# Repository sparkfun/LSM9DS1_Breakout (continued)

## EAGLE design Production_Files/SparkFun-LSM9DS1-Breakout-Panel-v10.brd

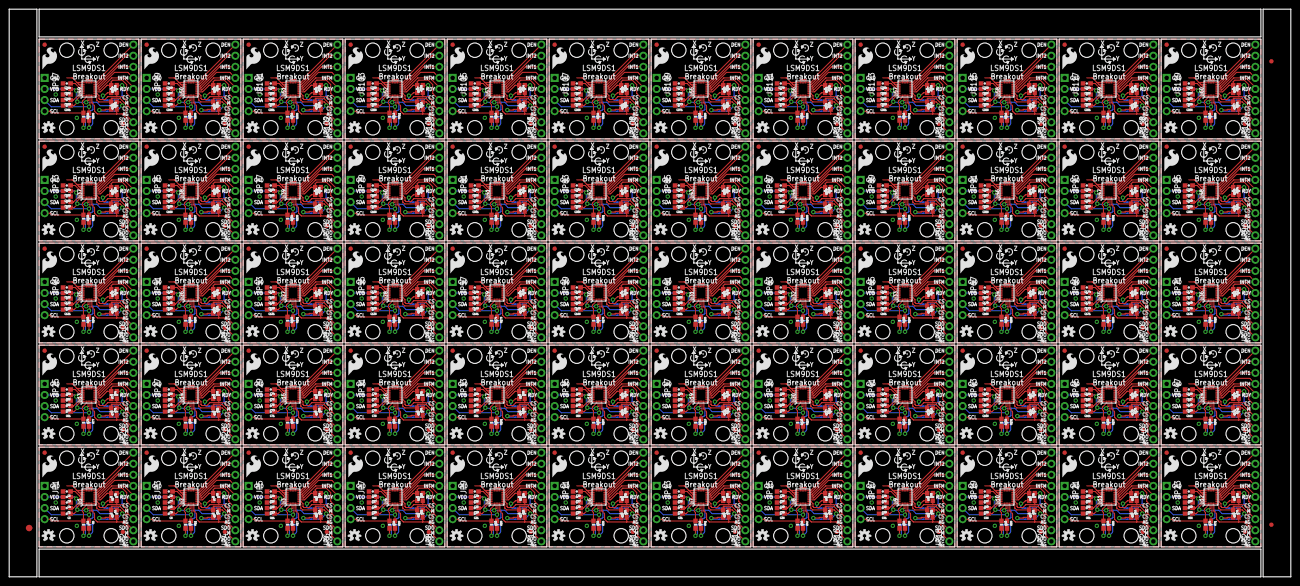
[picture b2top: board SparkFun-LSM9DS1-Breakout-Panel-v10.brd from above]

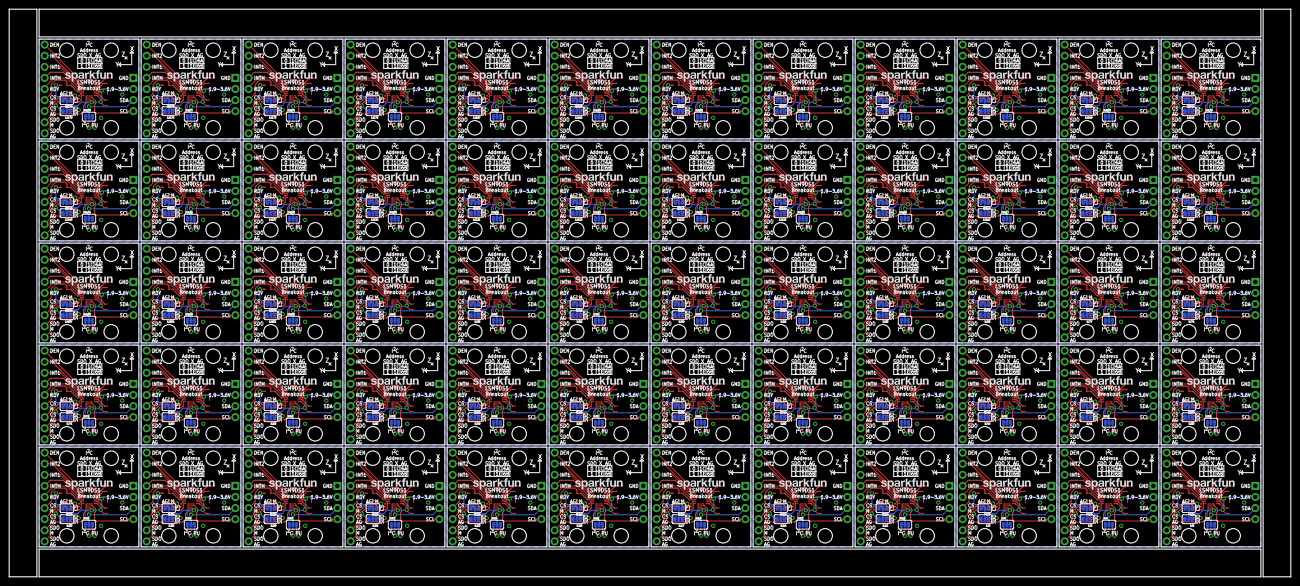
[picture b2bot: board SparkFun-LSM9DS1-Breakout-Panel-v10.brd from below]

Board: 2 copper layers, 293.6 x 130.0 mm, 1563 parts (240 on the bottom side), 1260 nets.

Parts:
C1, C2, C3, C6, C7, C8, C11, C12, C13, C16, C17, C18, C21, C22, C23, C26, C27, C28, C31, C32, C33, C36, C37, C38, C41, C42, C43, C46, C47, C48, C51, C52, C53, C56, C57, C58, C61, C62, C63, C66, C67, C68, C71, C72, C73, C76, C77, C78, C81, C82, C83, C86, C87, C88, C91, C92, C93, C96, C97, C98, C101, C102, C103, C106, C107, C108, C111, C112, C113, C116, C117, C118, C121, C122, C123, C126, C127, C128, C131, C132, C133, C136, C137, C138, C141, C142, C143, C146, C147, C148, C151, C152, C153, C156, C157, C158, C161, C162, C163, C166, C167, C168, C171, C172, C173, C176, C177, C178, C181, C182, C183, C186, C187, C188, C191, C192, C193, C196, C197, C198, C201, C202, C203, C206, C207, C208, C211, C212, C213, C216, C217, C218, C221, C222, C223, C226, C227, C228, C231, C232, C233, C236, C237, C238, C241, C242, C243, C246, C247, C248, C251, C252, C253, C256, C257, C258, C261, C262, C263, C266, C267, C268, C271, C272, C273, C276, C277, C278, C281, C282, C283, C286, C287, C288, C291, C292, C293, C296, C297, C298: 0.1uF; 0603-CAP
C4, C10, C15, C20, C25, C30, C35, C40, C45, C50, C55, C60, C65, C70, C75, C80, C85, C90, C95, C100, C105, C110, C115, C120, C125, C130, C135, C140, C145, C150, C155, C160, C165, C170, C175, C180, C185, C190, C195, C200, C205, C210, C215, C220, C225, C230, C235, C240, C245, C250, C255, C260, C265, C270, C275, C280, C285, C290, C295, C300: 10uF; 0603-CAP
C5, C9, C14, C19, C24, C29, C34, C39, C44, C49, C54, C59, C64, C69, C74, C79, C84, C89, C94, C99, C104, C109, C114, C119, C124, C129, C134, C139, C144, C149, C154, C159, C164, C169, C174, C179, C184, C189, C194, C199, C204, C209, C214, C219, C224, C229, C234, C239, C244, C249, C254, C259, C264, C269, C274, C279, C284, C289, C294, C299: 10nF; 0603-CAP
E$1: FIDUCIAL-1.5X3
E$4, E$5: FIDUCIAL-1X2
FID1, FID2, FID3, FID4, FID5, FID6, FID7, FID8, FID9, FID10, FID11, FID12, FID13, FID14, FID15, FID16, FID17, FID18, FID19, FID20, FID21, FID22, FID23, FID24, FID25, FID26, FID27, FID28, FID29, FID30, FID31, FID32, FID33, FID34, FID35, FID36, FID37, FID38, FID39, FID40, FID41, FID42, FID43, FID44, FID45, FID46, FID47, FID48, FID49, FID50, FID51, FID52, FID53, FID54, FID55, FID56, FID57, FID58, FID59, FID60, FID61, FID62, FID63, FID64, FID65, FID66, FID67, FID68, FID69, FID70, FID71, FID72, FID73, FID74, FID75, FID76, FID77, FID78, FID79, FID80, FID81, FID82, FID83, FID84, FID85, FID86, FID87, FID88, FID89, FID90, FID91, FID92, FID93, FID94, FID95, FID96, FID97, FID98, FID99, FID100, FID101, FID102, FID103, FID104, FID105, FID106, FID107, FID108, FID109, FID110, FID111, FID112, FID113, FID114, FID115, FID116, FID117, FID118, FID119, FID120: FIDUCIAL1X2; FIDUCIAL-1X2
JP1, JP3, JP5, JP7, JP9, JP11, JP13, JP15, JP17, JP19, JP21, JP23, JP25, JP27, JP29, JP31, JP33, JP35, JP37, JP39, JP41, JP43, JP45, JP47, JP49, JP51, JP53, JP55, JP57, JP59, JP61, JP63, JP65, JP67, JP69, JP71, JP73, JP75, JP77, JP79, JP81, JP83, JP85, JP87, JP89, JP91, JP93, JP95, JP97, JP99, JP101, JP103, JP105, JP107, JP109, JP111, JP113, JP115, JP117, JP119: 1X04_NO_SILK
JP2, JP4, JP6, JP8, JP10, JP12, JP14, JP16, JP18, JP20, JP22, JP24, JP26, JP28, JP30, JP32, JP34, JP36, JP38, JP40, JP42, JP44, JP46, JP48, JP50, JP52, JP54, JP56, JP58, JP60, JP62, JP64, JP66, JP68, JP70, JP72, JP74, JP76, JP78, JP80, JP82, JP84, JP86, JP88, JP90, JP92, JP94, JP96, JP98, JP100, JP102, JP104, JP106, JP108, JP110, JP112, JP114, JP116, JP118, JP120: M09NO_SILK; 1X09_NO_SILK
LOGO1, LOGO4, LOGO7, LOGO10, LOGO13, LOGO16, LOGO19, LOGO22, LOGO25, LOGO28, LOGO31, LOGO34, LOGO37, LOGO40, LOGO43, LOGO46, LOGO49, LOGO52, LOGO55, LOGO58, LOGO61, LOGO64, LOGO67, LOGO70, LOGO73, LOGO76, LOGO79, LOGO82, LOGO85, LOGO88, LOGO91, LOGO94, LOGO97, LOGO100, LOGO103, LOGO106, LOGO109, LOGO112, LOGO115, LOGO118, LOGO121, LOGO124, LOGO127, LOGO130, LOGO133, LOGO136, LOGO139, LOGO142, LOGO145, LOGO148, LOGO151, LOGO154, LOGO157, LOGO160, LOGO163, LOGO166, LOGO169, LOGO172, LOGO175, LOGO178: SFE_LOGO_NAME.1_INCH; SFE_LOGO_NAME_.1
LOGO2, LOGO5, LOGO8, LOGO11, LOGO14, LOGO17, LOGO20, LOGO23, LOGO26, LOGO29, LOGO32, LOGO35, LOGO38, LOGO41, LOGO44, LOGO47, LOGO50, LOGO53, LOGO56, LOGO59, LOGO62, LOGO65, LOGO68, LOGO71, LOGO74, LOGO77, LOGO80, LOGO83, LOGO86, LOGO89, LOGO92, LOGO95, LOGO98, LOGO101, LOGO104, LOGO107, LOGO110, LOGO113, LOGO116, LOGO119, LOGO122, LOGO125, LOGO128, LOGO131, LOGO134, LOGO137, LOGO140, LOGO143, LOGO146, LOGO149, LOGO152, LOGO155, LOGO158, LOGO161, LOGO164, LOGO167, LOGO170, LOGO173, LOGO176, LOGO179: SFE_LOGO_FLAME.2_INCH; SFE_LOGO_FLAME_.2
LOGO3, LOGO6, LOGO9, LOGO12, LOGO15, LOGO18, LOGO21, LOGO24, LOGO27, LOGO30, LOGO33, LOGO36, LOGO39, LOGO42, LOGO45, LOGO48, LOGO51, LOGO54, LOGO57, LOGO60, LOGO63, LOGO66, LOGO69, LOGO72, LOGO75, LOGO78, LOGO81, LOGO84, LOGO87, LOGO90, LOGO93, LOGO96, LOGO99, LOGO102, LOGO105, LOGO108, LOGO111, LOGO114, LOGO117, LOGO120, LOGO123, LOGO126, LOGO129, LOGO132, LOGO135, LOGO138, LOGO141, LOGO144, LOGO147, LOGO150, LOGO153, LOGO156, LOGO159, LOGO162, LOGO165, LOGO168, LOGO171, LOGO174, LOGO177, LOGO180: OSHW-LOGOS; OSHW-LOGO-S
R1, R2, R3, R4, R5, R6, R7, R8, R9, R10, R11, R12, R13, R14, R15, R16, R17, R18, R19, R20, R21, R22, R23, R24, R25, R26, R27, R28, R29, R30, R31, R32, R33, R34, R35, R36, R37, R38, R39, R40, R41, R42, R43, R44, R45, R46, R47, R48, R49, R50, R51, R52, R53, R54, R55, R56, R57, R58, R59, R60, R61, R62, R63, R64, R65, R66, R67, R68, R69, R70, R71, R72, R73, R74, R75, R76, R77, R78, R79, R80, R81, R82, R83, R84, R85, R86, R87, R88, R89, R90, R91, R92, R93, R94, R95, R96, R97, R98, R99, R100, R101, R102, R103, R104, R105, R106, R107, R108, R109, R110, R111, R112, R113, R114, R115, R116, R117, R118, R119, R120, R121, R122, R123, R124, R125, R126, R127, R128, R129, R130, R131, R132, R133, R134, R135, R136, R137, R138, R139, R140, R141, R142, R143, R144, R145, R146, R147, R148, R149, R150, R151, R152, R153, R154, R155, R156, R157, R158, R159, R160, R161, R162, R163, R164, R165, R166, R167, R168, R169, R170, R171, R172, R173, R174, R175, R176, R177, R178, R179, R180, R181, R182, R183, R184, R185, R186, R187, R188, R189, R190, R191, R192, R193, R194, R195, R196, R197, R198, R199, R200, R201, R202, R203, R204, R205, R206, R207, R208, R209, R210, R211, R212, R213, R214, R215, R216, R217, R218, R219, R220, R221, R222, R223, R224, R225, R226, R227, R228, R229, R230, R231, R232, R233, R234, R235, R236, R237, R238, R239, R240, R241, R242, R243, R244, R245, R246, R247, R248, R249, R250, R251, R252, R253, R254, R255, R256, R257, R258, R259, R260, R261, R262, R263, R264, R265, R266, R267, R268, R269, R270, R271, R272, R273, R274, R275, R276, R277, R278, R279, R280, R281, R282, R283, R284, R285, R286, R287, R288, R289, R290, R291, R292, R293, R294, R295, R296, R297, R298, R299, R300, R301, R302, R303, R304, R305, R306, R307, R308, R309, R310, R311, R312, R313, R314, R315, R316, R317, R318, R319, R320, R321, R322, R323, R324, R325, R326, R327, R328, R329, R330, R331, R332, R333, R334, R335, R336, R337, R338, R339, R340, R341, R342, R343, R344, R345, R346, R347, R348, R349, R350, R351, R352, R353, R354, R355, R356, R357, R358, R359, R360: 10K; 0603-RES
SJ1, SJ2, SJ3, SJ4, SJ5, SJ6, SJ7, SJ8, SJ9, SJ10, SJ11, SJ12, SJ13, SJ14, SJ15, SJ16, SJ17, SJ18, SJ19, SJ20, SJ21, SJ22, SJ23, SJ24, SJ25, SJ26, SJ27, SJ28, SJ29, SJ30, SJ31, SJ32, SJ33, SJ34, SJ35, SJ36, SJ37, SJ38, SJ39, SJ40, SJ41, SJ42, SJ43, SJ44, SJ45, SJ46, SJ47, SJ48, SJ49, SJ50, SJ51, SJ52, SJ53, SJ54, SJ55, SJ56, SJ57, SJ58, SJ59, SJ60, SJ61, SJ62, SJ63, SJ64, SJ65, SJ66, SJ67, SJ68, SJ69, SJ70, SJ71, SJ72, SJ73, SJ74, SJ75, SJ76, SJ77, SJ78, SJ79, SJ80, SJ81, SJ82, SJ83, SJ84, SJ85, SJ86, SJ87, SJ88, SJ89, SJ90, SJ91, SJ92, SJ93, SJ94, SJ95, SJ96, SJ97, SJ98, SJ99, SJ100, SJ101, SJ102, SJ103, SJ104, SJ105, SJ106, SJ107, SJ108, SJ109, SJ110, SJ111, SJ112, SJ113, SJ114, SJ115, SJ116, SJ117, SJ118, SJ119, SJ120, SJ121, SJ122, SJ123, SJ124, SJ125, SJ126, SJ127, SJ128, SJ129, SJ130, SJ131, SJ132, SJ133, SJ134, SJ135, SJ136, SJ137, SJ138, SJ139, SJ140, SJ141, SJ142, SJ143, SJ144, SJ145, SJ146, SJ147, SJ148, SJ149, SJ150, SJ151, SJ152, SJ153, SJ154, SJ155, SJ156, SJ157, SJ158, SJ159, SJ160, SJ161, SJ162, SJ163, SJ164, SJ165, SJ166, SJ167, SJ168, SJ169, SJ170, SJ171, SJ172, SJ173, SJ174, SJ175, SJ176, SJ177, SJ178, SJ179, SJ180: PAD-JUMPER-3-3OF3_NC_BY_TRACE_YES_SILK_FULL_BOX
STANDOFF1, STANDOFF2, STANDOFF3, STANDOFF4, STANDOFF5, STANDOFF6, STANDOFF7, STANDOFF8, STANDOFF9, STANDOFF10, STANDOFF11, STANDOFF12, STANDOFF13, STANDOFF14, STANDOFF15, STANDOFF16, STANDOFF17, STANDOFF18, STANDOFF19, STANDOFF20, STANDOFF21, STANDOFF22, STANDOFF23, STANDOFF24, STANDOFF25, STANDOFF26, STANDOFF27, STANDOFF28, STANDOFF29, STANDOFF30, STANDOFF31, STANDOFF32, STANDOFF33, STANDOFF34, STANDOFF35, STANDOFF36, STANDOFF37, STANDOFF38, STANDOFF39, STANDOFF40, STANDOFF41, STANDOFF42, STANDOFF43, STANDOFF44, STANDOFF45, STANDOFF46, STANDOFF47, STANDOFF48, STANDOFF49, STANDOFF50, STANDOFF51, STANDOFF52, STANDOFF53, STANDOFF54, STANDOFF55, STANDOFF56, STANDOFF57, STANDOFF58, STANDOFF59, STANDOFF60, STANDOFF61, STANDOFF62, STANDOFF63, STANDOFF64, STANDOFF65, STANDOFF66, STANDOFF67, STANDOFF68, STANDOFF69, STANDOFF70, STANDOFF71, STANDOFF72, STANDOFF73, STANDOFF74, STANDOFF75, STANDOFF76, STANDOFF77, STANDOFF78, STANDOFF79, STANDOFF80, STANDOFF81, STANDOFF82, STANDOFF83, STANDOFF84, STANDOFF85, STANDOFF86, STANDOFF87, STANDOFF88, STANDOFF89, STANDOFF90, STANDOFF91, STANDOFF92, STANDOFF93, STANDOFF94, STANDOFF95, STANDOFF96, STANDOFF97, STANDOFF98, STANDOFF99, STANDOFF100, STANDOFF101, STANDOFF102, STANDOFF103, STANDOFF104, STANDOFF105, STANDOFF106, STANDOFF107, STANDOFF108, STANDOFF109, STANDOFF110, STANDOFF111, STANDOFF112, STANDOFF113, STANDOFF114, STANDOFF115, STANDOFF116, STANDOFF117, STANDOFF118, STANDOFF119, STANDOFF120, STANDOFF121, STANDOFF122, STANDOFF123, STANDOFF124, STANDOFF125, STANDOFF126, STANDOFF127, STANDOFF128, STANDOFF129, STANDOFF130, STANDOFF131, STANDOFF132, STANDOFF133, STANDOFF134, STANDOFF135, STANDOFF136, STANDOFF137, STANDOFF138, STANDOFF139, STANDOFF140, STANDOFF141, STANDOFF142, STANDOFF143, STANDOFF144, STANDOFF145, STANDOFF146, STANDOFF147, STANDOFF148, STANDOFF149, STANDOFF150, STANDOFF151, STANDOFF152, STANDOFF153, STANDOFF154, STANDOFF155, STANDOFF156, STANDOFF157, STANDOFF158, STANDOFF159, STANDOFF160, STANDOFF161, STANDOFF162, STANDOFF163, STANDOFF164, STANDOFF165, STANDOFF166, STANDOFF167, STANDOFF168, STANDOFF169, STANDOFF170, STANDOFF171, STANDOFF172, STANDOFF173, STANDOFF174, STANDOFF175, STANDOFF176, STANDOFF177, STANDOFF178, STANDOFF179, STANDOFF180, STANDOFF181, STANDOFF182, STANDOFF183, STANDOFF184, STANDOFF185, STANDOFF186, STANDOFF187, STANDOFF188, STANDOFF189, STANDOFF190, STANDOFF191, STANDOFF192, STANDOFF193, STANDOFF194, STANDOFF195, STANDOFF196, STANDOFF197, STANDOFF198, STANDOFF199, STANDOFF200, STANDOFF201, STANDOFF202, STANDOFF203, STANDOFF204, STANDOFF205, STANDOFF206, STANDOFF207, STANDOFF208, STANDOFF209, STANDOFF210, STANDOFF211, STANDOFF212, STANDOFF213, STANDOFF214, STANDOFF215, STANDOFF216, STANDOFF217, STANDOFF218, STANDOFF219, STANDOFF220, STANDOFF221, STANDOFF222, STANDOFF223, STANDOFF224, STANDOFF225, STANDOFF226, STANDOFF227, STANDOFF228, STANDOFF229, STANDOFF230, STANDOFF231, STANDOFF232, STANDOFF233, STANDOFF234, STANDOFF235, STANDOFF236, STANDOFF237, STANDOFF238, STANDOFF239, STANDOFF240: STAND-OFF
U1, U2, U3, U4, U5, U6, U7, U8, U9, U10, U11, U12, U13, U14, U15, U16, U17, U18, U19, U20, U21, U22, U23, U24, U25, U26, U27, U28, U29, U30, U31, U32, U33, U34, U35, U36, U37, U38, U39, U40, U41, U42, U43, U44, U45, U46, U47, U48, U49, U50, U51, U52, U53, U54, U55, U56, U57, U58, U59, U60: LSM9DS1; LGA24-8X4

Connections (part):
C1: C1.1, U1.24
C2: C8.1, U2.24
C3: C13.1, U3.24
C4: C18.1, U4.24
C5: C23.1, U5.24
C6: C28.1, U6.24
C7: C33.1, U7.24
C8: C38.1, U8.24
C9: C43.1, U9.24
C10: C48.1, U10.24
C11: C53.1, U11.24
C12: C58.1, U12.24
C13: C63.1, U13.24
C14: C68.1, U14.24
C15: C73.1, U15.24
C16: C78.1, U16.24
C17: C83.1, U17.24
C18: C88.1, U18.24
C19: C93.1, U19.24
C20: C98.1, U20.24
C21: C103.1, U21.24
C22: C108.1, U22.24
C23: C113.1, U23.24
C24: C118.1, U24.24
C25: C123.1, U25.24
C26: C128.1, U26.24
C27: C133.1, U27.24
C28: C138.1, U28.24
C29: C143.1, U29.24
C30: C148.1, U30.24
C31: C153.1, U31.24
C32: C158.1, U32.24
C33: C163.1, U33.24
C34: C168.1, U34.24
C35: C173.1, U35.24
C36: C178.1, U36.24
C37: C183.1, U37.24
C38: C188.1, U38.24
C39: C193.1, U39.24
C40: C198.1, U40.24
C41: C203.1, U41.24
C42: C208.1, U42.24
C43: C213.1, U43.24
C44: C218.1, U44.24
C45: C223.1, U45.24
C46: C228.1, U46.24
C47: C233.1, U47.24
C48: C238.1, U48.24
C49: C243.1, U49.24
C50: C248.1, U50.24
C51: C253.1, U51.24
C52: C258.1, U52.24
C53: C263.1, U53.24
C54: C268.1, U54.24
C55: C273.1, U55.24
C56: C278.1, U56.24
C57: C283.1, U57.24
C58: C288.1, U58.24
C59: C293.1, U59.24
C60: C298.1, U60.24
CAP: C5.1, U1.21
CAP1: C9.1, U2.21
CAP2: C14.1, U3.21
CAP3: C19.1, U4.21
CAP4: C24.1, U5.21
CAP5: C29.1, U6.21
CAP6: C34.1, U7.21
CAP7: C39.1, U8.21
CAP8: C44.1, U9.21
CAP9: C49.1, U10.21
CAP10: C54.1, U11.21
CAP11: C59.1, U12.21
CAP12: C64.1, U13.21
CAP13: C69.1, U14.21
CAP14: C74.1, U15.21
CAP15: C79.1, U16.21
CAP16: C84.1, U17.21
CAP17: C89.1, U18.21
CAP18: C94.1, U19.21
CAP19: C99.1, U20.21
CAP20: C104.1, U21.21
CAP21: C109.1, U22.21
CAP22: C114.1, U23.21
CAP23: C119.1, U24.21
CAP24: C124.1, U25.21
CAP25: C129.1, U26.21
CAP26: C134.1, U27.21
CAP27: C139.1, U28.21
CAP28: C144.1, U29.21
CAP29: C149.1, U30.21
CAP30: C154.1, U31.21
CAP31: C159.1, U32.21
CAP32: C164.1, U33.21
CAP33: C169.1, U34.21
CAP34: C174.1, U35.21
CAP35: C179.1, U36.21
CAP36: C184.1, U37.21
CAP37: C189.1, U38.21
CAP38: C194.1, U39.21
CAP39: C199.1, U40.21
CAP40: C204.1, U41.21
CAP41: C209.1, U42.21
CAP42: C214.1, U43.21
CAP43: C219.1, U44.21
CAP44: C224.1, U45.21
CAP45: C229.1, U46.21
CAP46: C234.1, U47.21
CAP47: C239.1, U48.21
CAP48: C244.1, U49.21
CAP49: C249.1, U50.21
CAP50: C254.1, U51.21
CAP51: C259.1, U52.21
CAP52: C264.1, U53.21
CAP53: C269.1, U54.21
CAP54: C274.1, U55.21
CAP55: C279.1, U56.21
CAP56: C284.1, U57.21
CAP57: C289.1, U58.21
CAP58: C294.1, U59.21
CAP59: C299.1, U60.21
CS_A/G: JP2.3, R1.1, U1.7
CS_A/G1: JP4.3, R7.1, U2.7
CS_A/G2: JP6.3, R13.1, U3.7
CS_A/G3: JP8.3, R19.1, U4.7
CS_A/G4: JP10.3, R25.1, U5.7
CS_A/G5: JP12.3, R31.1, U6.7
CS_A/G6: JP14.3, R37.1, U7.7
CS_A/G7: JP16.3, R43.1, U8.7
CS_A/G8: JP18.3, R49.1, U9.7
CS_A/G9: JP20.3, R55.1, U10.7
CS_A/G10: JP22.3, R61.1, U11.7
CS_A/G11: JP24.3, R67.1, U12.7
CS_A/G12: JP26.3, R73.1, U13.7
CS_A/G13: JP28.3, R79.1, U14.7
CS_A/G14: JP30.3, R85.1, U15.7
CS_A/G15: JP32.3, R91.1, U16.7
CS_A/G16: JP34.3, R97.1, U17.7
CS_A/G17: JP36.3, R103.1, U18.7
CS_A/G18: JP38.3, R109.1, U19.7
CS_A/G19: JP40.3, R115.1, U20.7
CS_A/G20: JP42.3, R121.1, U21.7
CS_A/G21: JP44.3, R127.1, U22.7
CS_A/G22: JP46.3, R133.1, U23.7
CS_A/G23: JP48.3, R139.1, U24.7
CS_A/G24: JP50.3, R145.1, U25.7
CS_A/G25: JP52.3, R151.1, U26.7
CS_A/G26: JP54.3, R157.1, U27.7
CS_A/G27: JP56.3, R163.1, U28.7
CS_A/G28: JP58.3, R169.1, U29.7
CS_A/G29: JP60.3, R175.1, U30.7
CS_A/G30: JP62.3, R181.1, U31.7
CS_A/G31: JP64.3, R187.1, U32.7
CS_A/G32: JP66.3, R193.1, U33.7
CS_A/G33: JP68.3, R199.1, U34.7
CS_A/G34: JP70.3, R205.1, U35.7
CS_A/G35: JP72.3, R211.1, U36.7
CS_A/G36: JP74.3, R217.1, U37.7
CS_A/G37: JP76.3, R223.1, U38.7
CS_A/G38: JP78.3, R229.1, U39.7
CS_A/G39: JP80.3, R235.1, U40.7
CS_A/G40: JP82.3, R241.1, U41.7
CS_A/G41: JP84.3, R247.1, U42.7
CS_A/G42: JP86.3, R253.1, U43.7
CS_A/G43: JP88.3, R259.1, U44.7
CS_A/G44: JP90.3, R265.1, U45.7
CS_A/G45: JP92.3, R271.1, U46.7
CS_A/G46: JP94.3, R277.1, U47.7
CS_A/G47: JP96.3, R283.1, U48.7
CS_A/G48: JP98.3, R289.1, U49.7
CS_A/G49: JP100.3, R295.1, U50.7
CS_A/G50: JP102.3, R301.1, U51.7
CS_A/G51: JP104.3, R307.1, U52.7
CS_A/G52: JP106.3, R313.1, U53.7
CS_A/G53: JP108.3, R319.1, U54.7
CS_A/G54: JP110.3, R325.1, U55.7
CS_A/G55: JP112.3, R331.1, U56.7
CS_A/G56: JP114.3, R337.1, U57.7
CS_A/G57: JP116.3, R343.1, U58.7
CS_A/G58: JP118.3, R349.1, U59.7
CS_A/G59: JP120.3, R355.1, U60.7
CS_A/G_PU: R1.2, SJ1.3
CS_A/G_PU1: R7.2, SJ4.3
CS_A/G_PU2: R13.2, SJ7.3
CS_A/G_PU3: R19.2, SJ10.3
CS_A/G_PU4: R25.2, SJ13.3
CS_A/G_PU5: R31.2, SJ16.3
CS_A/G_PU6: R37.2, SJ19.3
CS_A/G_PU7: R43.2, SJ22.3
CS_A/G_PU8: R49.2, SJ25.3
CS_A/G_PU9: R55.2, SJ28.3
CS_A/G_PU10: R61.2, SJ31.3
CS_A/G_PU11: R67.2, SJ34.3
CS_A/G_PU12: R73.2, SJ37.3
CS_A/G_PU13: R79.2, SJ40.3
CS_A/G_PU14: R85.2, SJ43.3
CS_A/G_PU15: R91.2, SJ46.3
CS_A/G_PU16: R97.2, SJ49.3
CS_A/G_PU17: R103.2, SJ52.3
CS_A/G_PU18: R109.2, SJ55.3
CS_A/G_PU19: R115.2, SJ58.3
CS_A/G_PU20: R121.2, SJ61.3
CS_A/G_PU21: R127.2, SJ64.3
CS_A/G_PU22: R133.2, SJ67.3
CS_A/G_PU23: R139.2, SJ70.3
CS_A/G_PU24: R145.2, SJ73.3
CS_A/G_PU25: R151.2, SJ76.3
CS_A/G_PU26: R157.2, SJ79.3
CS_A/G_PU27: R163.2, SJ82.3
CS_A/G_PU28: R169.2, SJ85.3
CS_A/G_PU29: R175.2, SJ88.3
CS_A/G_PU30: R181.2, SJ91.3
CS_A/G_PU31: R187.2, SJ94.3
CS_A/G_PU32: R193.2, SJ97.3
CS_A/G_PU33: R199.2, SJ100.3
CS_A/G_PU34: R205.2, SJ103.3
CS_A/G_PU35: R211.2, SJ106.3
CS_A/G_PU36: R217.2, SJ109.3
CS_A/G_PU37: R223.2, SJ112.3
CS_A/G_PU38: R229.2, SJ115.3
CS_A/G_PU39: R235.2, SJ118.3
CS_A/G_PU40: R241.2, SJ121.3
CS_A/G_PU41: R247.2, SJ124.3
CS_A/G_PU42: R253.2, SJ127.3
CS_A/G_PU43: R259.2, SJ130.3
CS_A/G_PU44: R265.2, SJ133.3
CS_A/G_PU45: R271.2, SJ136.3
CS_A/G_PU46: R277.2, SJ139.3
CS_A/G_PU47: R283.2, SJ142.3
CS_A/G_PU48: R289.2, SJ145.3
CS_A/G_PU49: R295.2, SJ148.3
CS_A/G_PU50: R301.2, SJ151.3
CS_A/G_PU51: R307.2, SJ154.3
CS_A/G_PU52: R313.2, SJ157.3
CS_A/G_PU53: R319.2, SJ160.3
CS_A/G_PU54: R325.2, SJ163.3
CS_A/G_PU55: R331.2, SJ166.3
CS_A/G_PU56: R337.2, SJ169.3
CS_A/G_PU57: R343.2, SJ172.3
CS_A/G_PU58: R349.2, SJ175.3
CS_A/G_PU59: R355.2, SJ178.3
CS_M: JP2.4, R2.1, U1.8
CS_M1: JP4.4, R8.1, U2.8
CS_M2: JP6.4, R14.1, U3.8
CS_M3: JP8.4, R20.1, U4.8
CS_M4: JP10.4, R26.1, U5.8
CS_M5: JP12.4, R32.1, U6.8
CS_M6: JP14.4, R38.1, U7.8
CS_M7: JP16.4, R44.1, U8.8
CS_M8: JP18.4, R50.1, U9.8
CS_M9: JP20.4, R56.1, U10.8
CS_M10: JP22.4, R62.1, U11.8
CS_M11: JP24.4, R68.1, U12.8
CS_M12: JP26.4, R74.1, U13.8
CS_M13: JP28.4, R80.1, U14.8
CS_M14: JP30.4, R86.1, U15.8
CS_M15: JP32.4, R92.1, U16.8
CS_M16: JP34.4, R98.1, U17.8
CS_M17: JP36.4, R104.1, U18.8
CS_M18: JP38.4, R110.1, U19.8
CS_M19: JP40.4, R116.1, U20.8
CS_M20: JP42.4, R122.1, U21.8
CS_M21: JP44.4, R128.1, U22.8
CS_M22: JP46.4, R134.1, U23.8
CS_M23: JP48.4, R140.1, U24.8
CS_M24: JP50.4, R146.1, U25.8
CS_M25: JP52.4, R152.1, U26.8
CS_M26: JP54.4, R158.1, U27.8
CS_M27: JP56.4, R164.1, U28.8
CS_M28: JP58.4, R170.1, U29.8
CS_M29: JP60.4, R176.1, U30.8
CS_M30: JP62.4, R182.1, U31.8
CS_M31: JP64.4, R188.1, U32.8
CS_M32: JP66.4, R194.1, U33.8
CS_M33: JP68.4, R200.1, U34.8
CS_M34: JP70.4, R206.1, U35.8
CS_M35: JP72.4, R212.1, U36.8
CS_M36: JP74.4, R218.1, U37.8
CS_M37: JP76.4, R224.1, U38.8
CS_M38: JP78.4, R230.1, U39.8
CS_M39: JP80.4, R236.1, U40.8
CS_M40: JP82.4, R242.1, U41.8
CS_M41: JP84.4, R248.1, U42.8
CS_M42: JP86.4, R254.1, U43.8
CS_M43: JP88.4, R260.1, U44.8
CS_M44: JP90.4, R266.1, U45.8
CS_M45: JP92.4, R272.1, U46.8
CS_M46: JP94.4, R278.1, U47.8
CS_M47: JP96.4, R284.1, U48.8
CS_M48: JP98.4, R290.1, U49.8
CS_M49: JP100.4, R296.1, U50.8
CS_M50: JP102.4, R302.1, U51.8
CS_M51: JP104.4, R308.1, U52.8
CS_M52: JP106.4, R314.1, U53.8
CS_M53: JP108.4, R320.1, U54.8
CS_M54: JP110.4, R326.1, U55.8
CS_M55: JP112.4, R332.1, U56.8
CS_M56: JP114.4, R338.1, U57.8
CS_M57: JP116.4, R344.1, U58.8
CS_M58: JP118.4, R350.1, U59.8
CS_M59: JP120.4, R356.1, U60.8
CS_M_PU: R2.2, SJ1.1
CS_M_PU1: R8.2, SJ4.1
CS_M_PU2: R14.2, SJ7.1
CS_M_PU3: R20.2, SJ10.1
CS_M_PU4: R26.2, SJ13.1
CS_M_PU5: R32.2, SJ16.1
CS_M_PU6: R38.2, SJ19.1
CS_M_PU7: R44.2, SJ22.1
CS_M_PU8: R50.2, SJ25.1
CS_M_PU9: R56.2, SJ28.1
CS_M_PU10: R62.2, SJ31.1
CS_M_PU11: R68.2, SJ34.1
CS_M_PU12: R74.2, SJ37.1
CS_M_PU13: R80.2, SJ40.1
CS_M_PU14: R86.2, SJ43.1
CS_M_PU15: R92.2, SJ46.1
CS_M_PU16: R98.2, SJ49.1
CS_M_PU17: R104.2, SJ52.1
CS_M_PU18: R110.2, SJ55.1
CS_M_PU19: R116.2, SJ58.1
CS_M_PU20: R122.2, SJ61.1
CS_M_PU21: R128.2, SJ64.1
CS_M_PU22: R134.2, SJ67.1
CS_M_PU23: R140.2, SJ70.1
CS_M_PU24: R146.2, SJ73.1
CS_M_PU25: R152.2, SJ76.1
CS_M_PU26: R158.2, SJ79.1
CS_M_PU27: R164.2, SJ82.1
CS_M_PU28: R170.2, SJ85.1
CS_M_PU29: R176.2, SJ88.1
CS_M_PU30: R182.2, SJ91.1
CS_M_PU31: R188.2, SJ94.1
CS_M_PU32: R194.2, SJ97.1
CS_M_PU33: R200.2, SJ100.1
CS_M_PU34: R206.2, SJ103.1
CS_M_PU35: R212.2, SJ106.1
CS_M_PU36: R218.2, SJ109.1
CS_M_PU37: R224.2, SJ112.1
CS_M_PU38: R230.2, SJ115.1
CS_M_PU39: R236.2, SJ118.1
CS_M_PU40: R242.2, SJ121.1
CS_M_PU41: R248.2, SJ124.1
CS_M_PU42: R254.2, SJ127.1
CS_M_PU43: R260.2, SJ130.1
CS_M_PU44: R266.2, SJ133.1
CS_M_PU45: R272.2, SJ136.1
CS_M_PU46: R278.2, SJ139.1
CS_M_PU47: R284.2, SJ142.1
CS_M_PU48: R290.2, SJ145.1
CS_M_PU49: R296.2, SJ148.1
CS_M_PU50: R302.2, SJ151.1
CS_M_PU51: R308.2, SJ154.1
CS_M_PU52: R314.2, SJ157.1
CS_M_PU53: R320.2, SJ160.1
CS_M_PU54: R326.2, SJ163.1
CS_M_PU55: R332.2, SJ166.1
CS_M_PU56: R338.2, SJ169.1
CS_M_PU57: R344.2, SJ172.1
CS_M_PU58: R350.2, SJ175.1
CS_M_PU59: R356.2, SJ178.1
DEN_A/G: JP2.9, U1.13
DEN_A/G1: JP4.9, U2.13
DEN_A/G2: JP6.9, U3.13
DEN_A/G3: JP8.9, U4.13
DEN_A/G4: JP10.9, U5.13
DEN_A/G5: JP12.9, U6.13
DEN_A/G6: JP14.9, U7.13
DEN_A/G7: JP16.9, U8.13
DEN_A/G8: JP18.9, U9.13
DEN_A/G9: JP20.9, U10.13
DEN_A/G10: JP22.9, U11.13
DEN_A/G11: JP24.9, U12.13
DEN_A/G12: JP26.9, U13.13
DEN_A/G13: JP28.9, U14.13
DEN_A/G14: JP30.9, U15.13
DEN_A/G15: JP32.9, U16.13
DEN_A/G16: JP34.9, U17.13
DEN_A/G17: JP36.9, U18.13
DEN_A/G18: JP38.9, U19.13
DEN_A/G19: JP40.9, U20.13
DEN_A/G20: JP42.9, U21.13
DEN_A/G21: JP44.9, U22.13
DEN_A/G22: JP46.9, U23.13
DEN_A/G23: JP48.9, U24.13
DEN_A/G24: JP50.9, U25.13
DEN_A/G25: JP52.9, U26.13
DEN_A/G26: JP54.9, U27.13
DEN_A/G27: JP56.9, U28.13
DEN_A/G28: JP58.9, U29.13
DEN_A/G29: JP60.9, U30.13
DEN_A/G30: JP62.9, U31.13
DEN_A/G31: JP64.9, U32.13
DEN_A/G32: JP66.9, U33.13
DEN_A/G33: JP68.9, U34.13
DEN_A/G34: JP70.9, U35.13
DEN_A/G35: JP72.9, U36.13
DEN_A/G36: JP74.9, U37.13
DEN_A/G37: JP76.9, U38.13
DEN_A/G38: JP78.9, U39.13
DEN_A/G39: JP80.9, U40.13
DEN_A/G40: JP82.9, U41.13
DEN_A/G41: JP84.9, U42.13
DEN_A/G42: JP86.9, U43.13
DEN_A/G43: JP88.9, U44.13
DEN_A/G44: JP90.9, U45.13
DEN_A/G45: JP92.9, U46.13
DEN_A/G46: JP94.9, U47.13
DEN_A/G47: JP96.9, U48.13
DEN_A/G48: JP98.9, U49.13
DEN_A/G49: JP100.9, U50.13
DEN_A/G50: JP102.9, U51.13
DEN_A/G51: JP104.9, U52.13
DEN_A/G52: JP106.9, U53.13
DEN_A/G53: JP108.9, U54.13
DEN_A/G54: JP110.9, U55.13
DEN_A/G55: JP112.9, U56.13
DEN_A/G56: JP114.9, U57.13
DEN_A/G57: JP116.9, U58.13
DEN_A/G58: JP118.9, U59.13
DEN_A/G59: JP120.9, U60.13
DRDY_M: JP2.5, U1.9
DRDY_M1: JP4.5, U2.9
DRDY_M2: JP6.5, U3.9
DRDY_M3: JP8.5, U4.9
DRDY_M4: JP10.5, U5.9
DRDY_M5: JP12.5, U6.9
DRDY_M6: JP14.5, U7.9
DRDY_M7: JP16.5, U8.9
DRDY_M8: JP18.5, U9.9
DRDY_M9: JP20.5, U10.9
DRDY_M10: JP22.5, U11.9
DRDY_M11: JP24.5, U12.9
DRDY_M12: JP26.5, U13.9
DRDY_M13: JP28.5, U14.9
DRDY_M14: JP30.5, U15.9
DRDY_M15: JP32.5, U16.9
DRDY_M16: JP34.5, U17.9
DRDY_M17: JP36.5, U18.9
DRDY_M18: JP38.5, U19.9
DRDY_M19: JP40.5, U20.9
DRDY_M20: JP42.5, U21.9
DRDY_M21: JP44.5, U22.9
DRDY_M22: JP46.5, U23.9
DRDY_M23: JP48.5, U24.9
DRDY_M24: JP50.5, U25.9
DRDY_M25: JP52.5, U26.9
DRDY_M26: JP54.5, U27.9
DRDY_M27: JP56.5, U28.9
DRDY_M28: JP58.5, U29.9
DRDY_M29: JP60.5, U30.9
DRDY_M30: JP62.5, U31.9
DRDY_M31: JP64.5, U32.9
DRDY_M32: JP66.5, U33.9
DRDY_M33: JP68.5, U34.9
DRDY_M34: JP70.5, U35.9
DRDY_M35: JP72.5, U36.9
DRDY_M36: JP74.5, U37.9
DRDY_M37: JP76.5, U38.9
DRDY_M38: JP78.5, U39.9
DRDY_M39: JP80.5, U40.9
DRDY_M40: JP82.5, U41.9
DRDY_M41: JP84.5, U42.9
DRDY_M42: JP86.5, U43.9
DRDY_M43: JP88.5, U44.9
DRDY_M44: JP90.5, U45.9
DRDY_M45: JP92.5, U46.9
DRDY_M46: JP94.5, U47.9
DRDY_M47: JP96.5, U48.9
DRDY_M48: JP98.5, U49.9
DRDY_M49: JP100.5, U50.9
DRDY_M50: JP102.5, U51.9
DRDY_M51: JP104.5, U52.9
DRDY_M52: JP106.5, U53.9
DRDY_M53: JP108.5, U54.9
DRDY_M54: JP110.5, U55.9
DRDY_M55: JP112.5, U56.9
DRDY_M56: JP114.5, U57.9
DRDY_M57: JP116.5, U58.9
DRDY_M58: JP118.5, U59.9
DRDY_M59: JP120.5, U60.9
GND: C1.2, C2.2, C3.2, C4.2, C5.2, JP1.1, U1.14, U1.15, U1.16, U1.17, U1.18, U1.19, U1.20
GND1: C6.2, C7.2, C8.2, C9.2, C10.2, JP3.1, U2.14, U2.15, U2.16, U2.17, U2.18, U2.19, U2.20
GND2: C11.2, C12.2, C13.2, C14.2, C15.2, JP5.1, U3.14, U3.15, U3.16, U3.17, U3.18, U3.19, U3.20
GND3: C16.2, C17.2, C18.2, C19.2, C20.2, JP7.1, U4.14, U4.15, U4.16, U4.17, U4.18, U4.19, U4.20
GND4: C21.2, C22.2, C23.2, C24.2, C25.2, JP9.1, U5.14, U5.15, U5.16, U5.17, U5.18, U5.19, U5.20
GND5: C26.2, C27.2, C28.2, C29.2, C30.2, JP11.1, U6.14, U6.15, U6.16, U6.17, U6.18, U6.19, U6.20
GND6: C31.2, C32.2, C33.2, C34.2, C35.2, JP13.1, U7.14, U7.15, U7.16, U7.17, U7.18, U7.19, U7.20
GND7: C36.2, C37.2, C38.2, C39.2, C40.2, JP15.1, U8.14, U8.15, U8.16, U8.17, U8.18, U8.19, U8.20
GND8: C41.2, C42.2, C43.2, C44.2, C45.2, JP17.1, U9.14, U9.15, U9.16, U9.17, U9.18, U9.19, U9.20
GND9: C46.2, C47.2, C48.2, C49.2, C50.2, JP19.1, U10.14, U10.15, U10.16, U10.17, U10.18, U10.19, U10.20
GND10: C51.2, C52.2, C53.2, C54.2, C55.2, JP21.1, U11.14, U11.15, U11.16, U11.17, U11.18, U11.19, U11.20
GND11: C56.2, C57.2, C58.2, C59.2, C60.2, JP23.1, U12.14, U12.15, U12.16, U12.17, U12.18, U12.19, U12.20
GND12: C61.2, C62.2, C63.2, C64.2, C65.2, JP25.1, U13.14, U13.15, U13.16, U13.17, U13.18, U13.19, U13.20
GND13: C66.2, C67.2, C68.2, C69.2, C70.2, JP27.1, U14.14, U14.15, U14.16, U14.17, U14.18, U14.19, U14.20
GND14: C71.2, C72.2, C73.2, C74.2, C75.2, JP29.1, U15.14, U15.15, U15.16, U15.17, U15.18, U15.19, U15.20
GND15: C76.2, C77.2, C78.2, C79.2, C80.2, JP31.1, U16.14, U16.15, U16.16, U16.17, U16.18, U16.19, U16.20
GND16: C81.2, C82.2, C83.2, C84.2, C85.2, JP33.1, U17.14, U17.15, U17.16, U17.17, U17.18, U17.19, U17.20
GND17: C86.2, C87.2, C88.2, C89.2, C90.2, JP35.1, U18.14, U18.15, U18.16, U18.17, U18.18, U18.19, U18.20
GND18: C91.2, C92.2, C93.2, C94.2, C95.2, JP37.1, U19.14, U19.15, U19.16, U19.17, U19.18, U19.19, U19.20
GND19: C96.2, C97.2, C98.2, C99.2, C100.2, JP39.1, U20.14, U20.15, U20.16, U20.17, U20.18, U20.19, U20.20
GND20: C101.2, C102.2, C103.2, C104.2, C105.2, JP41.1, U21.14, U21.15, U21.16, U21.17, U21.18, U21.19, U21.20
GND21: C106.2, C107.2, C108.2, C109.2, C110.2, JP43.1, U22.14, U22.15, U22.16, U22.17, U22.18, U22.19, U22.20
GND22: C111.2, C112.2, C113.2, C114.2, C115.2, JP45.1, U23.14, U23.15, U23.16, U23.17, U23.18, U23.19, U23.20
GND23: C116.2, C117.2, C118.2, C119.2, C120.2, JP47.1, U24.14, U24.15, U24.16, U24.17, U24.18, U24.19, U24.20
GND24: C121.2, C122.2, C123.2, C124.2, C125.2, JP49.1, U25.14, U25.15, U25.16, U25.17, U25.18, U25.19, U25.20
GND25: C126.2, C127.2, C128.2, C129.2, C130.2, JP51.1, U26.14, U26.15, U26.16, U26.17, U26.18, U26.19, U26.20
GND26: C131.2, C132.2, C133.2, C134.2, C135.2, JP53.1, U27.14, U27.15, U27.16, U27.17, U27.18, U27.19, U27.20
GND27: C136.2, C137.2, C138.2, C139.2, C140.2, JP55.1, U28.14, U28.15, U28.16, U28.17, U28.18, U28.19, U28.20
GND28: C141.2, C142.2, C143.2, C144.2, C145.2, JP57.1, U29.14, U29.15, U29.16, U29.17, U29.18, U29.19, U29.20
GND29: C146.2, C147.2, C148.2, C149.2, C150.2, JP59.1, U30.14, U30.15, U30.16, U30.17, U30.18, U30.19, U30.20
GND30: C151.2, C152.2, C153.2, C154.2, C155.2, JP61.1, U31.14, U31.15, U31.16, U31.17, U31.18, U31.19, U31.20
GND31: C156.2, C157.2, C158.2, C159.2, C160.2, JP63.1, U32.14, U32.15, U32.16, U32.17, U32.18, U32.19, U32.20
GND32: C161.2, C162.2, C163.2, C164.2, C165.2, JP65.1, U33.14, U33.15, U33.16, U33.17, U33.18, U33.19, U33.20
GND33: C166.2, C167.2, C168.2, C169.2, C170.2, JP67.1, U34.14, U34.15, U34.16, U34.17, U34.18, U34.19, U34.20
GND34: C171.2, C172.2, C173.2, C174.2, C175.2, JP69.1, U35.14, U35.15, U35.16, U35.17, U35.18, U35.19, U35.20
GND35: C176.2, C177.2, C178.2, C179.2, C180.2, JP71.1, U36.14, U36.15, U36.16, U36.17, U36.18, U36.19, U36.20
GND36: C181.2, C182.2, C183.2, C184.2, C185.2, JP73.1, U37.14, U37.15, U37.16, U37.17, U37.18, U37.19, U37.20
GND37: C186.2, C187.2, C188.2, C189.2, C190.2, JP75.1, U38.14, U38.15, U38.16, U38.17, U38.18, U38.19, U38.20
GND38: C191.2, C192.2, C193.2, C194.2, C195.2, JP77.1, U39.14, U39.15, U39.16, U39.17, U39.18, U39.19, U39.20
GND39: C196.2, C197.2, C198.2, C199.2, C200.2, JP79.1, U40.14, U40.15, U40.16, U40.17, U40.18, U40.19, U40.20
GND40: C201.2, C202.2, C203.2, C204.2, C205.2, JP81.1, U41.14, U41.15, U41.16, U41.17, U41.18, U41.19, U41.20
GND41: C206.2, C207.2, C208.2, C209.2, C210.2, JP83.1, U42.14, U42.15, U42.16, U42.17, U42.18, U42.19, U42.20
GND42: C211.2, C212.2, C213.2, C214.2, C215.2, JP85.1, U43.14, U43.15, U43.16, U43.17, U43.18, U43.19, U43.20
GND43: C216.2, C217.2, C218.2, C219.2, C220.2, JP87.1, U44.14, U44.15, U44.16, U44.17, U44.18, U44.19, U44.20
GND44: C221.2, C222.2, C223.2, C224.2, C225.2, JP89.1, U45.14, U45.15, U45.16, U45.17, U45.18, U45.19, U45.20
GND45: C226.2, C227.2, C228.2, C229.2, C230.2, JP91.1, U46.14, U46.15, U46.16, U46.17, U46.18, U46.19, U46.20
GND46: C231.2, C232.2, C233.2, C234.2, C235.2, JP93.1, U47.14, U47.15, U47.16, U47.17, U47.18, U47.19, U47.20
GND47: C236.2, C237.2, C238.2, C239.2, C240.2, JP95.1, U48.14, U48.15, U48.16, U48.17, U48.18, U48.19, U48.20
GND48: C241.2, C242.2, C243.2, C244.2, C245.2, JP97.1, U49.14, U49.15, U49.16, U49.17, U49.18, U49.19, U49.20
GND49: C246.2, C247.2, C248.2, C249.2, C250.2, JP99.1, U50.14, U50.15, U50.16, U50.17, U50.18, U50.19, U50.20
GND50: C251.2, C252.2, C253.2, C254.2, C255.2, JP101.1, U51.14, U51.15, U51.16, U51.17, U51.18, U51.19, U51.20
GND51: C256.2, C257.2, C258.2, C259.2, C260.2, JP103.1, U52.14, U52.15, U52.16, U52.17, U52.18, U52.19, U52.20
GND52: C261.2, C262.2, C263.2, C264.2, C265.2, JP105.1, U53.14, U53.15, U53.16, U53.17, U53.18, U53.19, U53.20
GND53: C266.2, C267.2, C268.2, C269.2, C270.2, JP107.1, U54.14, U54.15, U54.16, U54.17, U54.18, U54.19, U54.20
GND54: C271.2, C272.2, C273.2, C274.2, C275.2, JP109.1, U55.14, U55.15, U55.16, U55.17, U55.18, U55.19, U55.20
GND55: C276.2, C277.2, C278.2, C279.2, C280.2, JP111.1, U56.14, U56.15, U56.16, U56.17, U56.18, U56.19, U56.20
GND56: C281.2, C282.2, C283.2, C284.2, C285.2, JP113.1, U57.14, U57.15, U57.16, U57.17, U57.18, U57.19, U57.20
GND57: C286.2, C287.2, C288.2, C289.2, C290.2, JP115.1, U58.14, U58.15, U58.16, U58.17, U58.18, U58.19, U58.20
GND58: C291.2, C292.2, C293.2, C294.2, C295.2, JP117.1, U59.14, U59.15, U59.16, U59.17, U59.18, U59.19, U59.20
GND59: C296.2, C297.2, C298.2, C299.2, C300.2, JP119.1, U60.14, U60.15, U60.16, U60.17, U60.18, U60.19, U60.20
INT1_A/G: JP2.7, U1.11
INT1_A/G1: JP4.7, U2.11
INT1_A/G2: JP6.7, U3.11
INT1_A/G3: JP8.7, U4.11
INT1_A/G4: JP10.7, U5.11
INT1_A/G5: JP12.7, U6.11
INT1_A/G6: JP14.7, U7.11
INT1_A/G7: JP16.7, U8.11
INT1_A/G8: JP18.7, U9.11
INT1_A/G9: JP20.7, U10.11
INT1_A/G10: JP22.7, U11.11
INT1_A/G11: JP24.7, U12.11
INT1_A/G12: JP26.7, U13.11
INT1_A/G13: JP28.7, U14.11
INT1_A/G14: JP30.7, U15.11
INT1_A/G15: JP32.7, U16.11
INT1_A/G16: JP34.7, U17.11
INT1_A/G17: JP36.7, U18.11
INT1_A/G18: JP38.7, U19.11
INT1_A/G19: JP40.7, U20.11
INT1_A/G20: JP42.7, U21.11
INT1_A/G21: JP44.7, U22.11
INT1_A/G22: JP46.7, U23.11
INT1_A/G23: JP48.7, U24.11
INT1_A/G24: JP50.7, U25.11
INT1_A/G25: JP52.7, U26.11
INT1_A/G26: JP54.7, U27.11
INT1_A/G27: JP56.7, U28.11
INT1_A/G28: JP58.7, U29.11
INT1_A/G29: JP60.7, U30.11
INT1_A/G30: JP62.7, U31.11
INT1_A/G31: JP64.7, U32.11
INT1_A/G32: JP66.7, U33.11
INT1_A/G33: JP68.7, U34.11
INT1_A/G34: JP70.7, U35.11
INT1_A/G35: JP72.7, U36.11
INT1_A/G36: JP74.7, U37.11
INT1_A/G37: JP76.7, U38.11
INT1_A/G38: JP78.7, U39.11
INT1_A/G39: JP80.7, U40.11
INT1_A/G40: JP82.7, U41.11
INT1_A/G41: JP84.7, U42.11
INT1_A/G42: JP86.7, U43.11
INT1_A/G43: JP88.7, U44.11
INT1_A/G44: JP90.7, U45.11
INT1_A/G45: JP92.7, U46.11
INT1_A/G46: JP94.7, U47.11
INT1_A/G47: JP96.7, U48.11
INT1_A/G48: JP98.7, U49.11
INT1_A/G49: JP100.7, U50.11
INT1_A/G50: JP102.7, U51.11
INT1_A/G51: JP104.7, U52.11
INT1_A/G52: JP106.7, U53.11
INT1_A/G53: JP108.7, U54.11
INT1_A/G54: JP110.7, U55.11
INT1_A/G55: JP112.7, U56.11
INT1_A/G56: JP114.7, U57.11
INT1_A/G57: JP116.7, U58.11
INT1_A/G58: JP118.7, U59.11
INT1_A/G59: JP120.7, U60.11
INT2_A/G: JP2.8, U1.12
INT2_A/G1: JP4.8, U2.12
INT2_A/G2: JP6.8, U3.12
INT2_A/G3: JP8.8, U4.12
INT2_A/G4: JP10.8, U5.12
INT2_A/G5: JP12.8, U6.12
INT2_A/G6: JP14.8, U7.12
INT2_A/G7: JP16.8, U8.12
INT2_A/G8: JP18.8, U9.12
INT2_A/G9: JP20.8, U10.12
INT2_A/G10: JP22.8, U11.12
INT2_A/G11: JP24.8, U12.12
INT2_A/G12: JP26.8, U13.12
INT2_A/G13: JP28.8, U14.12
INT2_A/G14: JP30.8, U15.12
INT2_A/G15: JP32.8, U16.12
INT2_A/G16: JP34.8, U17.12
INT2_A/G17: JP36.8, U18.12
INT2_A/G18: JP38.8, U19.12
INT2_A/G19: JP40.8, U20.12
INT2_A/G20: JP42.8, U21.12
INT2_A/G21: JP44.8, U22.12
INT2_A/G22: JP46.8, U23.12
INT2_A/G23: JP48.8, U24.12
INT2_A/G24: JP50.8, U25.12
INT2_A/G25: JP52.8, U26.12
INT2_A/G26: JP54.8, U27.12
INT2_A/G27: JP56.8, U28.12
INT2_A/G28: JP58.8, U29.12
INT2_A/G29: JP60.8, U30.12
INT2_A/G30: JP62.8, U31.12
INT2_A/G31: JP64.8, U32.12
INT2_A/G32: JP66.8, U33.12
INT2_A/G33: JP68.8, U34.12
INT2_A/G34: JP70.8, U35.12
INT2_A/G35: JP72.8, U36.12
INT2_A/G36: JP74.8, U37.12
INT2_A/G37: JP76.8, U38.12
INT2_A/G38: JP78.8, U39.12
INT2_A/G39: JP80.8, U40.12
INT2_A/G40: JP82.8, U41.12
INT2_A/G41: JP84.8, U42.12
INT2_A/G42: JP86.8, U43.12
INT2_A/G43: JP88.8, U44.12
INT2_A/G44: JP90.8, U45.12
INT2_A/G45: JP92.8, U46.12
INT2_A/G46: JP94.8, U47.12
INT2_A/G47: JP96.8, U48.12
INT2_A/G48: JP98.8, U49.12
INT2_A/G49: JP100.8, U50.12
INT2_A/G50: JP102.8, U51.12
INT2_A/G51: JP104.8, U52.12
INT2_A/G52: JP106.8, U53.12
INT2_A/G53: JP108.8, U54.12
INT2_A/G54: JP110.8, U55.12
INT2_A/G55: JP112.8, U56.12
INT2_A/G56: JP114.8, U57.12
INT2_A/G57: JP116.8, U58.12
INT2_A/G58: JP118.8, U59.12
INT2_A/G59: JP120.8, U60.12
INT_M: JP2.6, U1.10
INT_M1: JP4.6, U2.10
INT_M2: JP6.6, U3.10
INT_M3: JP8.6, U4.10
INT_M4: JP10.6, U5.10
INT_M5: JP12.6, U6.10
INT_M6: JP14.6, U7.10
INT_M7: JP16.6, U8.10
INT_M8: JP18.6, U9.10
INT_M9: JP20.6, U10.10
INT_M10: JP22.6, U11.10
INT_M11: JP24.6, U12.10
INT_M12: JP26.6, U13.10
INT_M13: JP28.6, U14.10
INT_M14: JP30.6, U15.10
INT_M15: JP32.6, U16.10
INT_M16: JP34.6, U17.10
INT_M17: JP36.6, U18.10
INT_M18: JP38.6, U19.10
INT_M19: JP40.6, U20.10
INT_M20: JP42.6, U21.10
INT_M21: JP44.6, U22.10
INT_M22: JP46.6, U23.10
INT_M23: JP48.6, U24.10
INT_M24: JP50.6, U25.10
INT_M25: JP52.6, U26.10
INT_M26: JP54.6, U27.10
INT_M27: JP56.6, U28.10
INT_M28: JP58.6, U29.10
INT_M29: JP60.6, U30.10
INT_M30: JP62.6, U31.10
INT_M31: JP64.6, U32.10
INT_M32: JP66.6, U33.10
INT_M33: JP68.6, U34.10
INT_M34: JP70.6, U35.10
INT_M35: JP72.6, U36.10
INT_M36: JP74.6, U37.10
INT_M37: JP76.6, U38.10
INT_M38: JP78.6, U39.10
INT_M39: JP80.6, U40.10
INT_M40: JP82.6, U41.10
INT_M41: JP84.6, U42.10
INT_M42: JP86.6, U43.10
INT_M43: JP88.6, U44.10
INT_M44: JP90.6, U45.10
INT_M45: JP92.6, U46.10
INT_M46: JP94.6, U47.10
INT_M47: JP96.6, U48.10
INT_M48: JP98.6, U49.10
INT_M49: JP100.6, U50.10
INT_M50: JP102.6, U51.10
INT_M51: JP104.6, U52.10
INT_M52: JP106.6, U53.10
INT_M53: JP108.6, U54.10
INT_M54: JP110.6, U55.10
INT_M55: JP112.6, U56.10
INT_M56: JP114.6, U57.10
INT_M57: JP116.6, U58.10
INT_M58: JP118.6, U59.10
INT_M59: JP120.6, U60.10
SCL: JP1.4, R6.1, U1.2
SCL1: JP3.4, R12.1, U2.2
SCL2: JP5.4, R18.1, U3.2
SCL3: JP7.4, R24.1, U4.2
SCL4: JP9.4, R30.1, U5.2
SCL5: JP11.4, R36.1, U6.2
SCL6: JP13.4, R42.1, U7.2
SCL7: JP15.4, R48.1, U8.2
SCL8: JP17.4, R54.1, U9.2
SCL9: JP19.4, R60.1, U10.2
SCL10: JP21.4, R66.1, U11.2
SCL11: JP23.4, R72.1, U12.2
SCL12: JP25.4, R78.1, U13.2
SCL13: JP27.4, R84.1, U14.2
SCL14: JP29.4, R90.1, U15.2
SCL15: JP31.4, R96.1, U16.2
SCL16: JP33.4, R102.1, U17.2
SCL17: JP35.4, R108.1, U18.2
SCL18: JP37.4, R114.1, U19.2
SCL19: JP39.4, R120.1, U20.2
SCL20: JP41.4, R126.1, U21.2
SCL21: JP43.4, R132.1, U22.2
SCL22: JP45.4, R138.1, U23.2
SCL23: JP47.4, R144.1, U24.2
SCL24: JP49.4, R150.1, U25.2
SCL25: JP51.4, R156.1, U26.2
SCL26: JP53.4, R162.1, U27.2
SCL27: JP55.4, R168.1, U28.2
SCL28: JP57.4, R174.1, U29.2
SCL29: JP59.4, R180.1, U30.2
SCL30: JP61.4, R186.1, U31.2
SCL31: JP63.4, R192.1, U32.2
SCL32: JP65.4, R198.1, U33.2
SCL33: JP67.4, R204.1, U34.2
SCL34: JP69.4, R210.1, U35.2
SCL35: JP71.4, R216.1, U36.2
SCL36: JP73.4, R222.1, U37.2
SCL37: JP75.4, R228.1, U38.2
SCL38: JP77.4, R234.1, U39.2
SCL39: JP79.4, R240.1, U40.2
SCL40: JP81.4, R246.1, U41.2
SCL41: JP83.4, R252.1, U42.2
SCL42: JP85.4, R258.1, U43.2
SCL43: JP87.4, R264.1, U44.2
SCL44: JP89.4, R270.1, U45.2
SCL45: JP91.4, R276.1, U46.2
SCL46: JP93.4, R282.1, U47.2
SCL47: JP95.4, R288.1, U48.2
SCL48: JP97.4, R294.1, U49.2
SCL49: JP99.4, R300.1, U50.2
SCL50: JP101.4, R306.1, U51.2
SCL51: JP103.4, R312.1, U52.2
SCL52: JP105.4, R318.1, U53.2
SCL53: JP107.4, R324.1, U54.2
SCL54: JP109.4, R330.1, U55.2
SCL55: JP111.4, R336.1, U56.2
SCL56: JP113.4, R342.1, U57.2
SCL57: JP115.4, R348.1, U58.2
SCL58: JP117.4, R354.1, U59.2
SCL59: JP119.4, R360.1, U60.2
SCL_PU: R6.2, SJ3.3
SCL_PU1: R12.2, SJ6.3
SCL_PU2: R18.2, SJ9.3
SCL_PU3: R24.2, SJ12.3
SCL_PU4: R30.2, SJ15.3
SCL_PU5: R36.2, SJ18.3
SCL_PU6: R42.2, SJ21.3
SCL_PU7: R48.2, SJ24.3
SCL_PU8: R54.2, SJ27.3
SCL_PU9: R60.2, SJ30.3
SCL_PU10: R66.2, SJ33.3
SCL_PU11: R72.2, SJ36.3
SCL_PU12: R78.2, SJ39.3
SCL_PU13: R84.2, SJ42.3
SCL_PU14: R90.2, SJ45.3
SCL_PU15: R96.2, SJ48.3
SCL_PU16: R102.2, SJ51.3
SCL_PU17: R108.2, SJ54.3
SCL_PU18: R114.2, SJ57.3
SCL_PU19: R120.2, SJ60.3
SCL_PU20: R126.2, SJ63.3
SCL_PU21: R132.2, SJ66.3
SCL_PU22: R138.2, SJ69.3
SCL_PU23: R144.2, SJ72.3
SCL_PU24: R150.2, SJ75.3
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
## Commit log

2015-02-04 Initial commit of hardware.
2015-02-09 Cleaning up schematic.
2015-02-09 Adding board mesurements, fixing some traces, labelling VCC range.
2015-03-02 Re-arranging some silk. Updating board to v10.
2015-03-02 Moving silk, adding GND vias, adding axis to bottom silk. Updating version to v10.
2015-03-06 created panel v10
2015-08-13 Adding product info to readme.
2015-08-13 Renaming directories.
2015-08-13 Adding v1.0 product release tag link
2015-08-13 Squashed 'Libraries/Arduino/' content from commit 05cbe7b
    git-subtree-dir: Libraries/Arduino
    git-subtree-split: 05cbe7b8abbc9820736a54fdd6d2550e56e6d7b8
2015-08-13 Adding README to Libraries folder.
2015-08-13 Squashed 'Libraries/Particle/' content from commit ecfc112
    git-subtree-dir: Libraries/Particle
    git-subtree-split: ecfc112d754a973d1518fb4fa33e839a53bcadf1
2015-08-13 Adding Particle library to readme
2018-08-20 Correct Temperature Calculation
    Updated how temperature is calculated according to the datasheet.
2018-08-24 Temperature Read Error
    Corrected method for reading temperature.
2018-08-24 Code optimization
    Removed unnecessary while loops.
2018-08-27 Sync With LSM9DS1 Arduino Library
    Updated the following to bring it inline with Arduino Library:
    -Added return statements that prevent compilation in certain IDEs.
    -Updated how temperature is calculated.
2018-08-27 Correcting Heading Calculation
    Corrected heading calculation that was producing a range over 360 degrees.
2018-08-27 Heading Correction
    Corrected error in calculating heading that resulted in a range greater than 360 degrees.
2023-11-01 Fixes some minor discrepancies in return values, removes unused values or uninitialized arrays, rolls version, re-zips Arduino source files
